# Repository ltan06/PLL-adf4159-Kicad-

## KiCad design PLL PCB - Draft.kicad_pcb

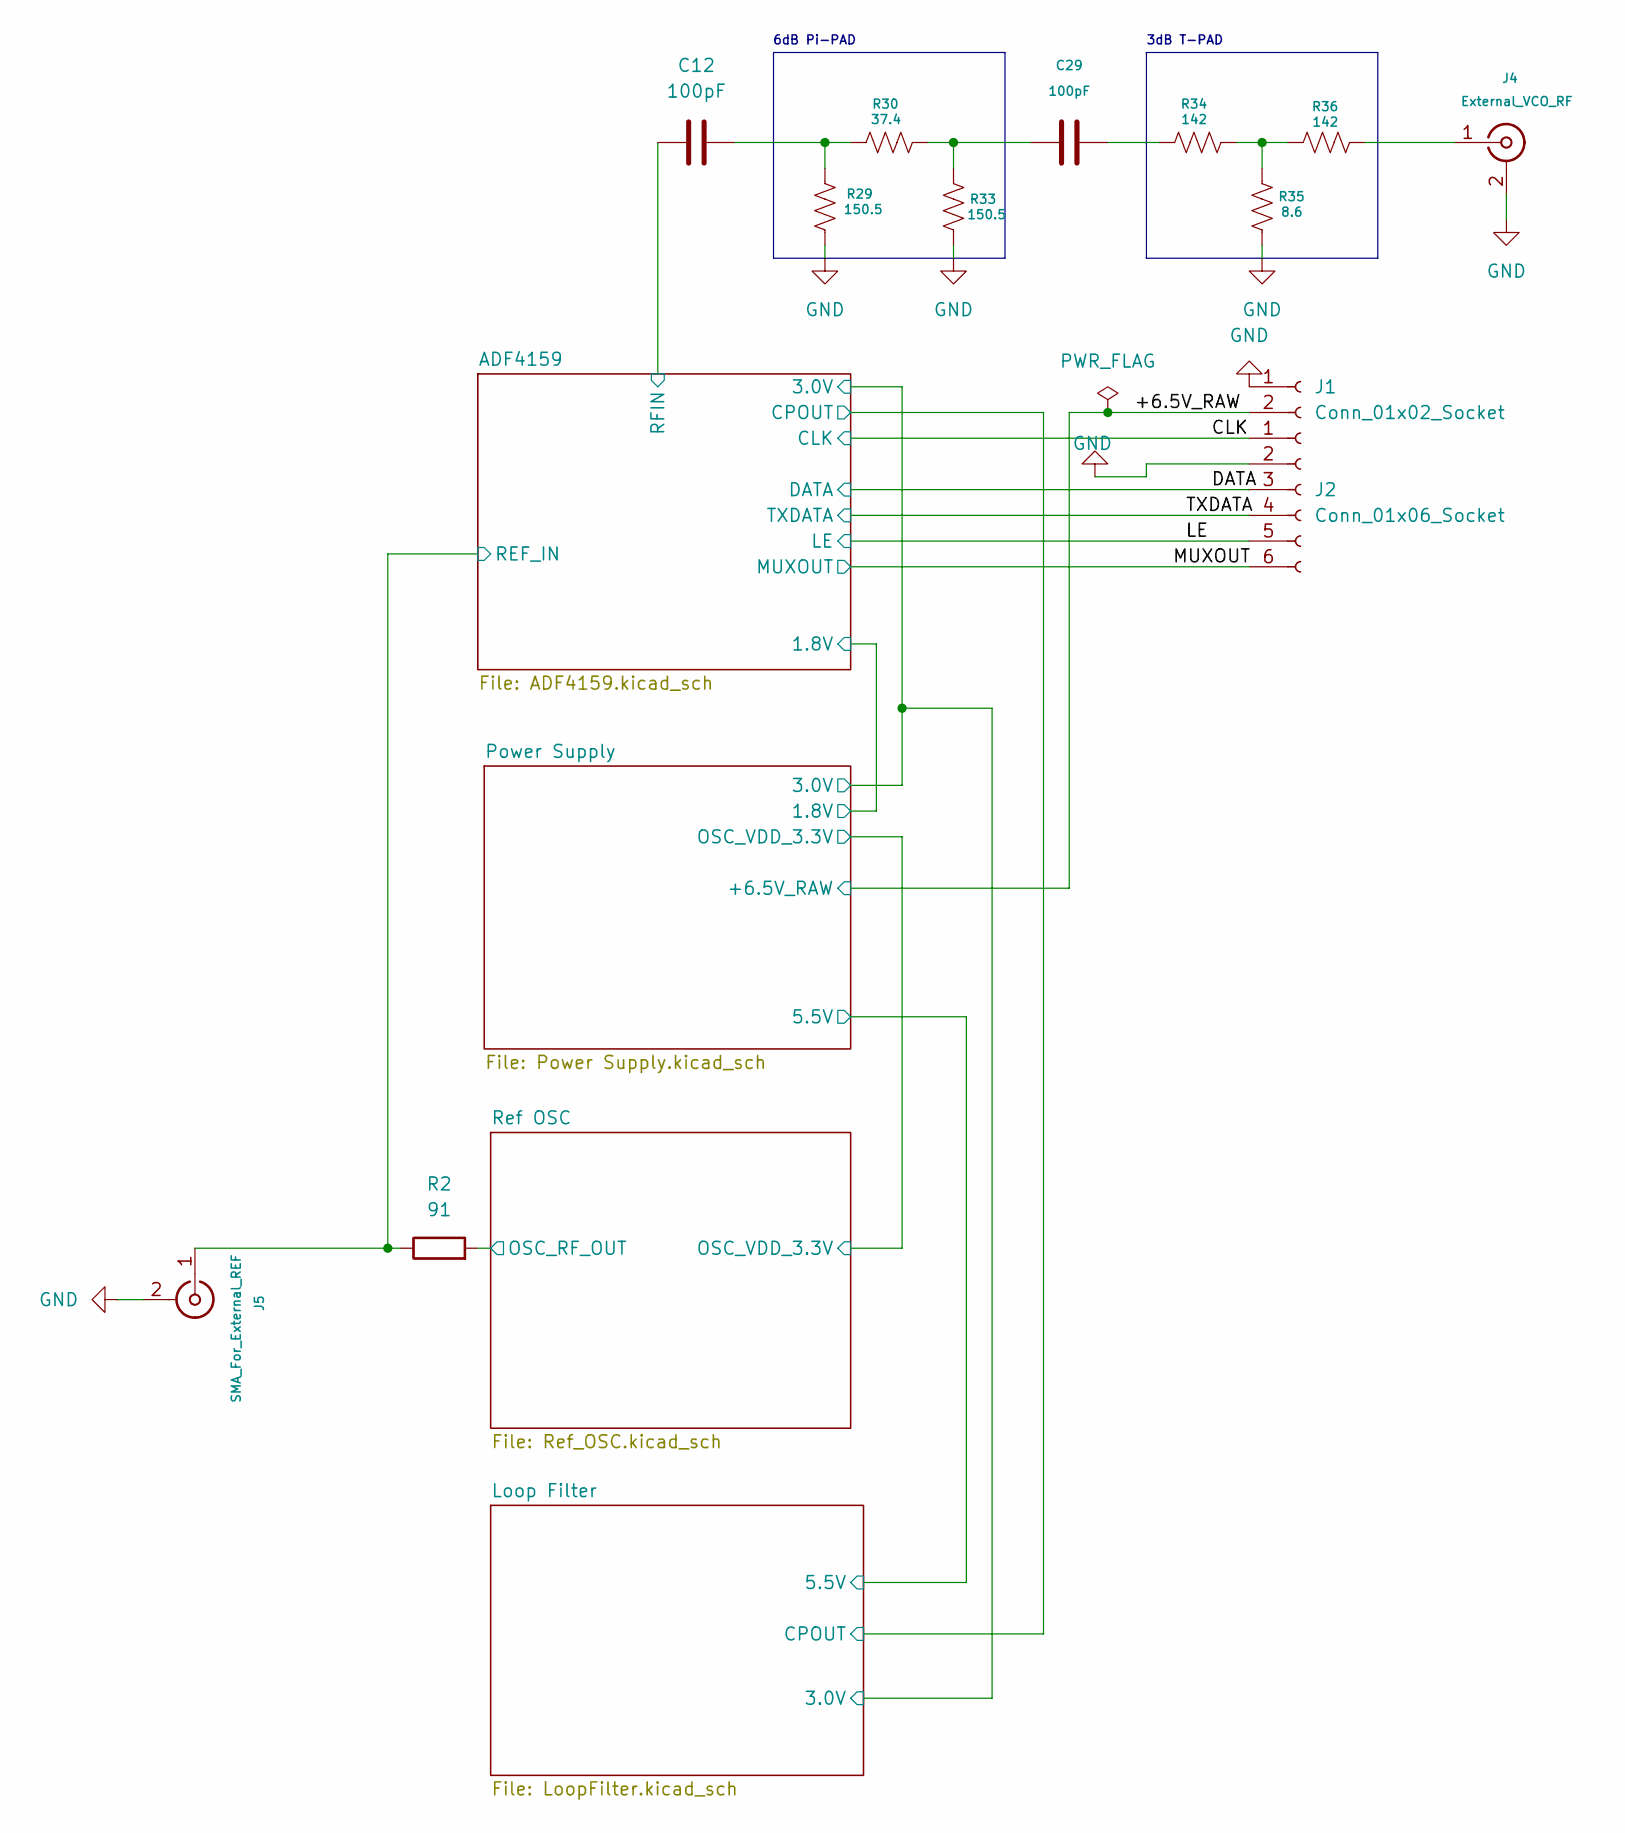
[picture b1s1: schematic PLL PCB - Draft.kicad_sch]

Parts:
C12, C29: 100pF; C_0402_1005Metric
J1: Conn_01x02_Socket; PinSocket_1x02_P2.54mm_Vertical
J2: Conn_01x06_Socket; PinSocket_2x03_P2.54mm_Vertical
J4: External_VCO_RF; SMA_EDGELAUNCH
J5: SMA_For_External_REF; SMA_EDGELAUNCH
R2: 91; R_0402_1005Metric
R29, R33: 150.5; R_0402_1005Metric
R30: 37.4; R_0402_1005Metric
R34, R36: 142; R_0402_1005Metric
R35: 8.6; R_0402_1005Metric

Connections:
/+6.5V_RAW: J1.2; also elsewhere on the board
/ADF4159/REF_IN: J5.1 (In), J5.P, R2.1; also elsewhere on the board
/ADF4159/RFIN: C12.1; also elsewhere on the board
/CLK: J2.1; also elsewhere on the board
/DATA: J2.3; also elsewhere on the board
/LE: J2.5; also elsewhere on the board
/MUXOUT: J2.6; also elsewhere on the board
/Ref OSC/OSC_RF_OUT: R2.2; also elsewhere on the board
/TXDATA: J2.4; also elsewhere on the board
GND: J1.1, J2.2, J4.2 (Ext), J4.GND@1, J4.GND@2, J4.GND@3, J4.GND@4, J5.2 (Ext), J5.GND@1, J5.GND@2, J5.GND@3, J5.GND@4, R29.2, R33.2, R35.2; also elsewhere on the board
unnamed: C12.2, R29.1, R30.1
unnamed: C29.1, R30.2, R33.1
unnamed: C29.2, R34.1
unnamed: J4.1 (In), J4.P, R36.2
unnamed: R34.2, R35.1, R36.1

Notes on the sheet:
6dB Pi-PAD
3dB T-PAD

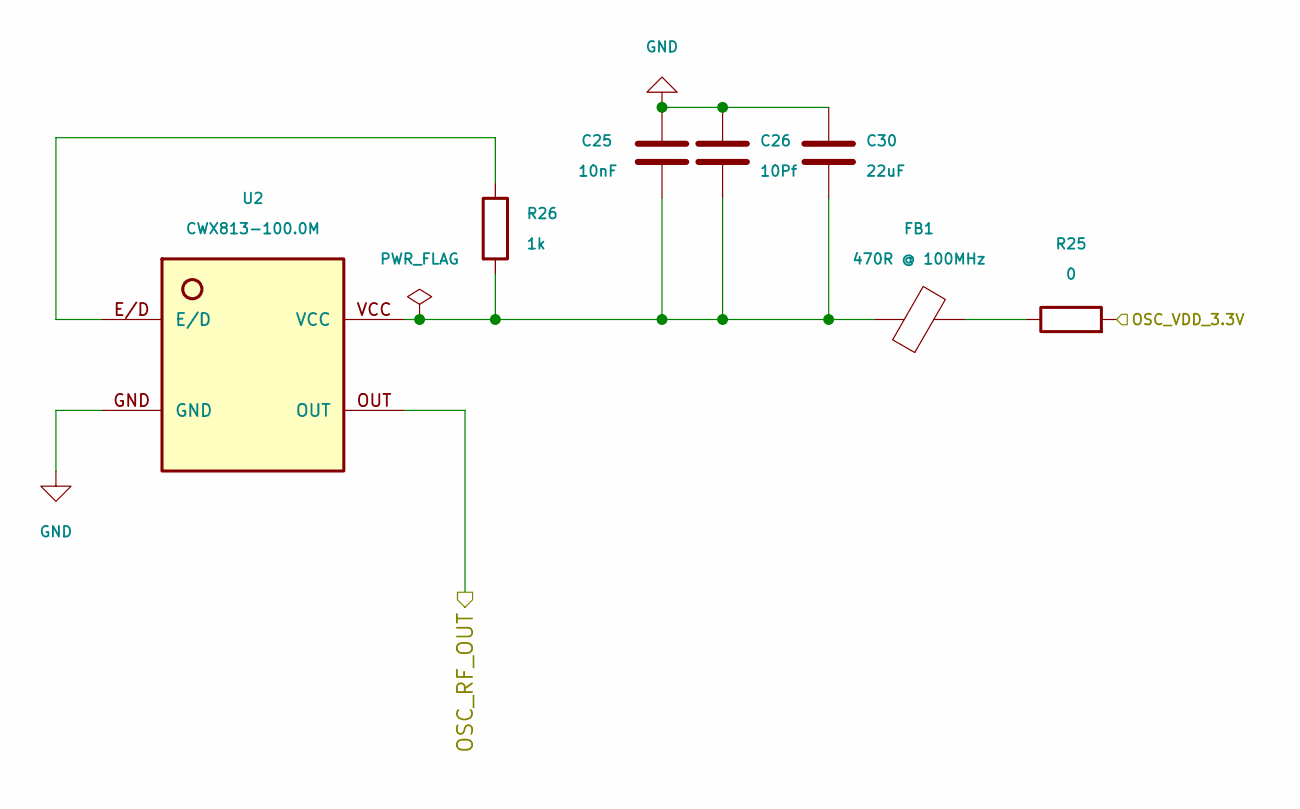
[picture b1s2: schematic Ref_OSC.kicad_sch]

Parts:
C25: 10nF; C_0402_1005Metric
C26: 10Pf; C_0402_1005Metric
C30: 22uF; C_0402_1005Metric
FB1: 470R @ 100MHz; L_0402_1005Metric
R25: 0; R_0402_1005Metric
R26: 1k; R_0402_1005Metric
U2: CWX813-100.0M; SMT-5X7

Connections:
/Power Supply/OSC_VDD_3.3V: R25.2; also elsewhere on the board
/Ref OSC/OSC_RF_OUT: U2.OUT; also elsewhere on the board
GND: C25.1, C26.1, C30.1, U2.GND; also elsewhere on the board
unnamed: C25.2, C26.2, C30.2, FB1.1, R26.2, U2.VCC
unnamed: FB1.2, R25.1
unnamed: R26.1, U2.E/D

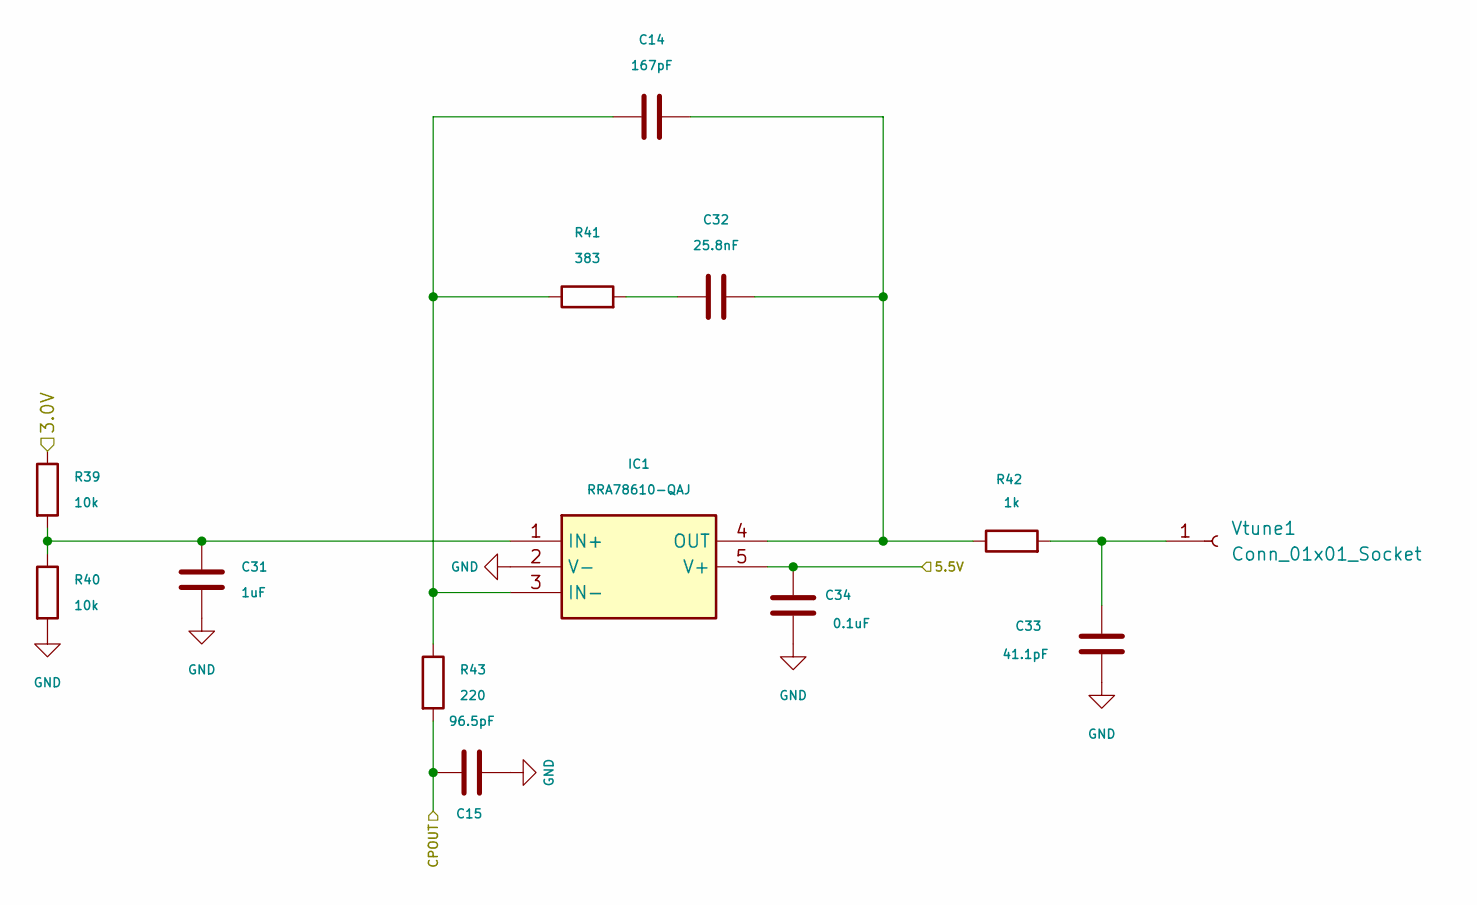
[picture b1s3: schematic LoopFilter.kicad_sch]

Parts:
C14: 167pF; C_0402_1005Metric
C15: 96.5pF; C_0402_1005Metric
C31: 1uF; C_0402_1005Metric
C32: 25.8nF; C_0402_1005Metric
C33: 41.1pF; C_0402_1005Metric
C34: 0.1uF; C_0402_1005Metric
IC1: RRA78610-QAJ; SOT-353_SC-70-5; Manufacturer_Part_Number RRA78610-QAJ
R39, R40: 10k; R_0402_1005Metric
R41: 383; R_0402_1005Metric
R42: 1k; R_0402_1005Metric
R43: 220; R_0402_1005Metric
Vtune1: Conn_01x01_Socket; PinSocket_1x01_P2.54mm_Vertical

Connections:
/ADF4159/3.0V: R39.1; also elsewhere on the board
/ADF4159/CPOUT: C15.2, R43.2; also elsewhere on the board
/Loop Filter/5.5V: C34.1, IC1.5 (V+); also elsewhere on the board
GND: C15.1, C31.2, C33.1, C34.2, IC1.2 (V-), R40.2; also elsewhere on the board
unnamed: C32.1, R41.2
unnamed: C31.1, IC1.1 (IN+), R39.2, R40.1
unnamed: C14.1, IC1.3 (IN-), R41.1, R43.1
unnamed: C14.2, C32.2, IC1.4 (OUT), R42.1
unnamed: C33.2, R42.2, Vtune1.1 (Pin_1_1)

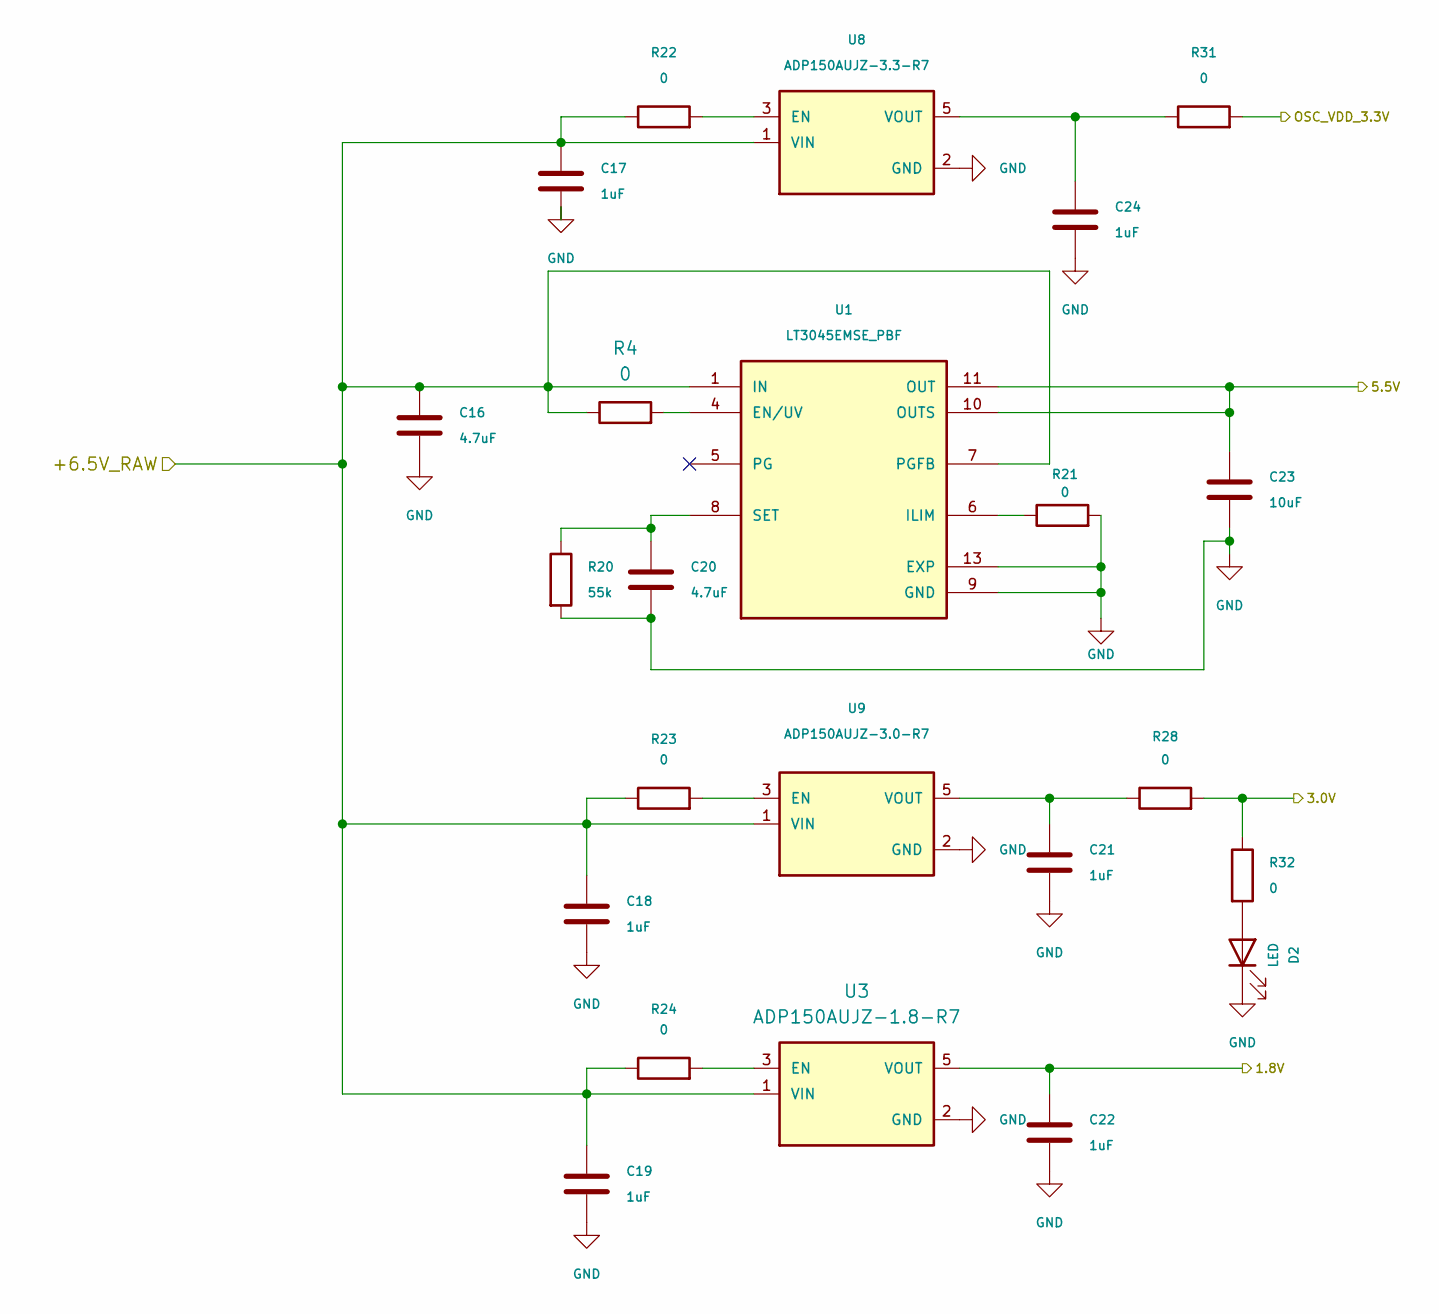
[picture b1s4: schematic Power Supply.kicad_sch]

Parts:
C16, C20: 4.7uF; C_0402_1005Metric
C17, C18, C19, C21, C22, C24: 1uF; C_0402_1005Metric
C23: 10uF; C_0402_1005Metric
D2: LED; LED_0603_1608Metric
R4, R21, R22, R23, R24, R28, R31, R32: 0; R_0402_1005Metric
R20: 55k; R_0402_1005Metric
U1: LT3045EMSE_PBF; MSOP-12-1EP_3x4.039mm_P0.65mm_EP1.651x2.845mm_ThermalVias; PARTREV D
U3: ADP150AUJZ-1.8-R7; SOT95P280X100-5N
U8: ADP150AUJZ-3.3-R7; SOT95P280X100-5N
U9: ADP150AUJZ-3.0-R7; SOT95P280X100-5N

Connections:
/+6.5V_RAW: C16.1, C17.1, C18.1, C19.1, R4.1, R22.1, R23.1, R24.1, U1.1 (IN), U1.2 (IN), U1.3 (IN), U1.7 (PGFB), U3.1 (VIN), U8.1 (VIN), U9.1 (VIN); also elsewhere on the board
/ADF4159/1.8V: C22.1, U3.5 (VOUT); also elsewhere on the board
/ADF4159/3.0V: R28.2, R32.1; also elsewhere on the board
/Loop Filter/5.5V: C23.1, U1.10 (OUTS), U1.11 (OUT), U1.12 (OUT); also elsewhere on the board
/Power Supply/OSC_VDD_3.3V: R31.2; also elsewhere on the board
GND: C16.2, C17.2, C18.2, C19.2, C20.2, C21.2, C22.2, C23.2, C24.2, D2.1 (K), R20.2, R21.2, U1.9 (GND), U1.13 (EXP), U3.2 (GND), U8.2 (GND), U9.2 (GND); also elsewhere on the board
unnamed: D2.2 (A), R32.2
unnamed: R4.2, U1.4 (EN/UV)
unnamed: R21.1, U1.6 (ILIM)
unnamed: C20.1, R20.1, U1.8 (SET)
unnamed: R24.2, U3.3 (EN)
unnamed: R22.2, U8.3 (EN)
unnamed: C24.1, R31.1, U8.5 (VOUT)
unnamed: R23.2, U9.3 (EN)
unnamed: C21.1, R28.1, U9.5 (VOUT)

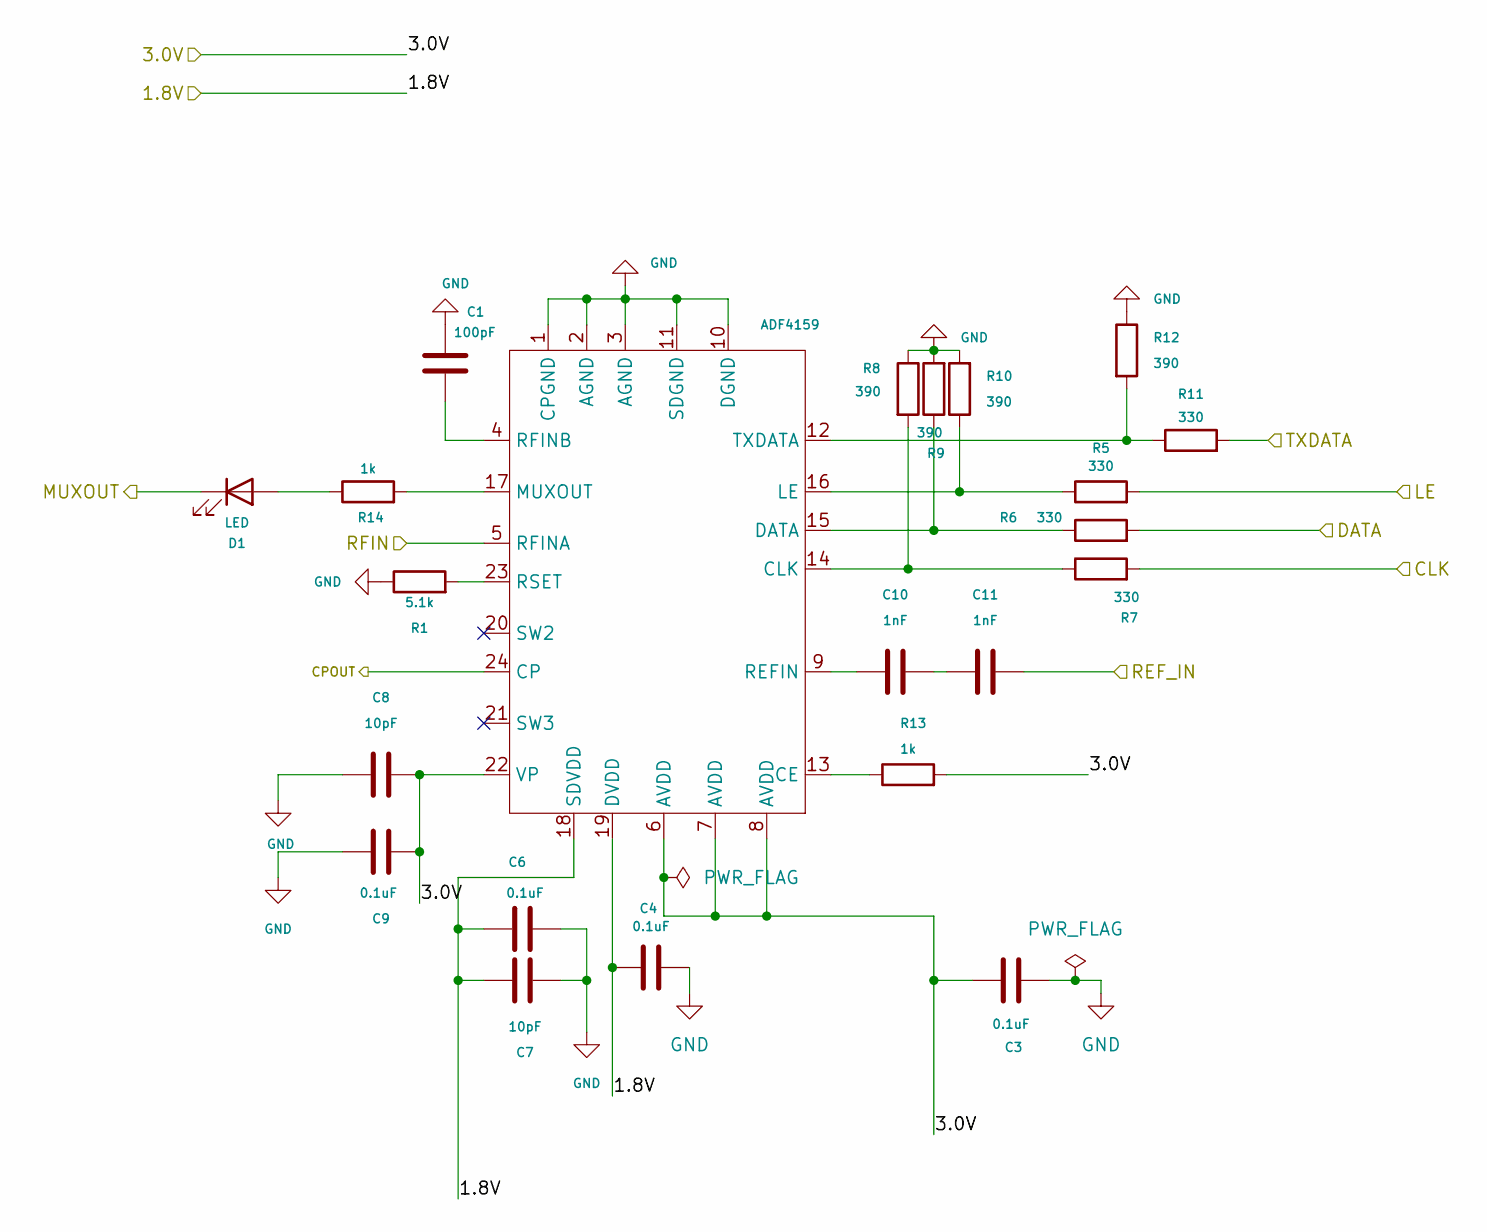
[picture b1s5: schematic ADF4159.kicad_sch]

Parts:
ADF4159: LFCSP-24-1EP_4x4mm_P0.5mm_EP2.5x2.5mm
C1: 100pF; C_0402_1005Metric
C3, C4, C6, C9: 0.1uF; C_0402_1005Metric
C7, C8: 10pF; C_0402_1005Metric
C10, C11: 1nF; C_0402_1005Metric
D1: LED; LED_0402_1005Metric
R1: 5.1k; R_0402_1005Metric
R5, R6, R7, R11: 330; R_0402_1005Metric
R8, R9, R10, R12: 390; R_0402_1005Metric
R13, R14: 1k; R_0402_1005Metric

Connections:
/ADF4159/1.8V: ADF4159.18 (SDVDD), ADF4159.19 (DVDD), C4.2, C6.1, C7.1; also elsewhere on the board
/ADF4159/3.0V: ADF4159.6 (AVDD), ADF4159.7 (AVDD), ADF4159.8 (AVDD), ADF4159.22 (VP), C3.1, C8.2, C9.2, R13.2; also elsewhere on the board
/ADF4159/CPOUT: ADF4159.24 (CP); also elsewhere on the board
/ADF4159/REF_IN: C11.2; also elsewhere on the board
/ADF4159/RFIN: ADF4159.5 (RFINA); also elsewhere on the board
/CLK: R7.2; also elsewhere on the board
/DATA: R6.2; also elsewhere on the board
/LE: R5.2; also elsewhere on the board
/MUXOUT: D1.1 (K); also elsewhere on the board
/TXDATA: R11.2; also elsewhere on the board
GND: ADF4159.1 (CPGND), ADF4159.2 (AGND), ADF4159.3 (AGND), ADF4159.10 (DGND), ADF4159.11 (SDGND), C1.1, C3.2, C4.1, C6.2, C7.2, C8.1, C9.1, R1.1, R8.1, R9.2, R10.2, R12.1; also elsewhere on the board
unnamed: ADF4159.13 (CE), R13.1
unnamed: ADF4159.14 (CLK), R7.1, R8.2
unnamed: ADF4159.15 (DATA), R6.1, R9.1
unnamed: ADF4159.16 (LE), R5.1, R10.1
unnamed: ADF4159.17 (MUXOUT), R14.2
unnamed: ADF4159.9 (REFIN), C10.1
unnamed: ADF4159.4 (RFINB), C1.2
unnamed: ADF4159.23 (RSET), R1.2
unnamed: ADF4159.12 (TXDATA), R11.1, R12.2
unnamed: C10.2, C11.1
unnamed: D1.2 (A), R14.1

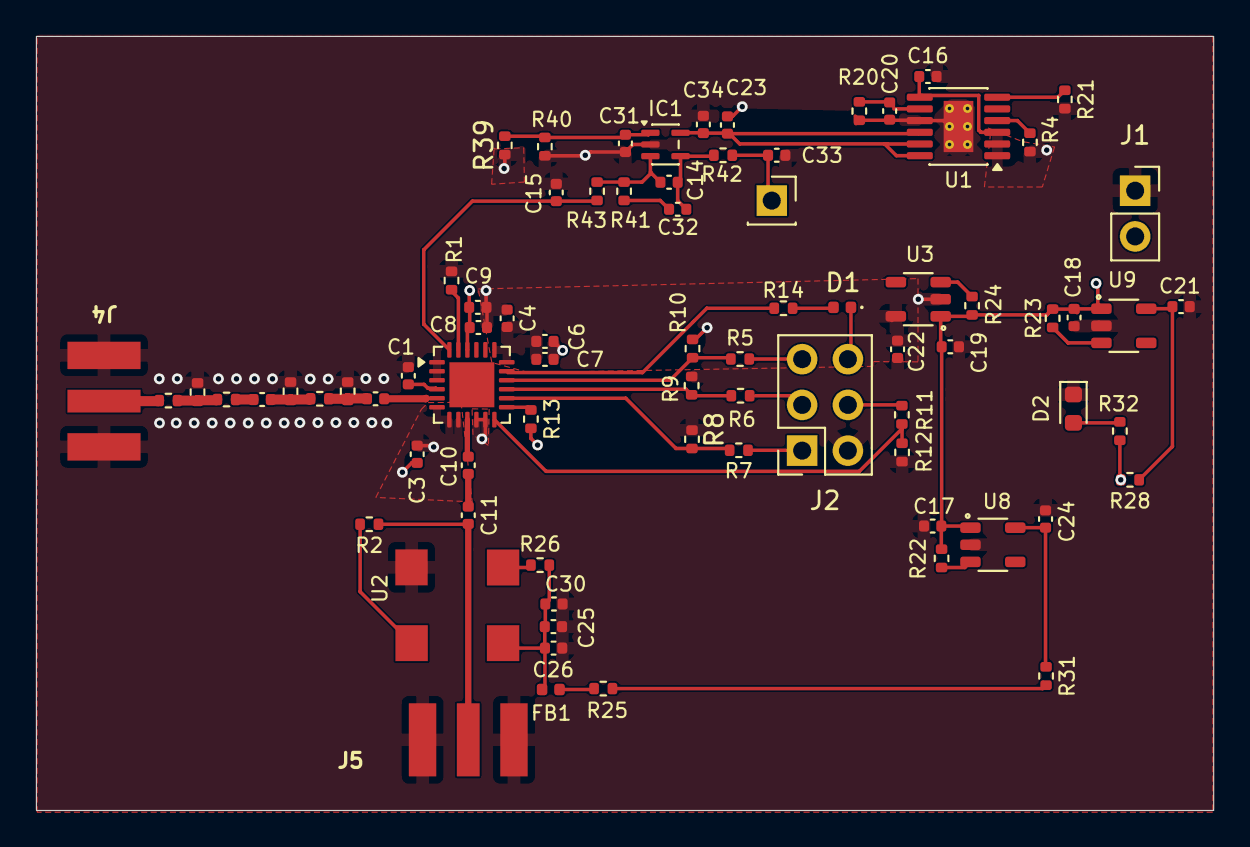
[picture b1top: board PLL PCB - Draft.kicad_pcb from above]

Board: 4 copper layers, 65.4 x 43.0 mm, 78 parts (0 on the bottom side), 48 nets.
